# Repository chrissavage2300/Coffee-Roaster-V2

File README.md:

# Coffee-Roaster-V2
My Second DIY coffee roaster

Parts not listed on BOM:

Intake fan: BL4447-04W-B49

https://www.aliexpress.us/item/2251800670595894.html?spm=a2g0o.order_list.order_list_main.29.4b841802Pr1vyz&gatewayAdapt=glo2usa

Exhaust fan: 4090D 12V

https://www.aliexpress.us/item/3256805403626998.html?spm=a2g0o.order_list.order_list_main.195.4b841802Pr1vyz&gatewayAdapt=glo2usa

SSR: GSR1-1-25DA

https://www.aliexpress.us/item/3256802111187964.html?spm=a2g0o.order_list.order_list_main.60.4b841802Pr1vyz&gatewayAdapt=glo2usa

Gears for drum: 1M40T-Bore 6 mm

https://www.aliexpress.us/item/2255800052157775.html?spm=a2g0o.order_list.order_list_main.88.4b841802Pr1vyz&gatewayAdapt=glo2usa

Drum Motor: 12V Single Motor, 66RPM

https://www.aliexpress.us/item/3256805242242724.html?spm=a2g0o.order_list.order_list_main.205.4b841802Pr1vyz&gatewayAdapt=glo2usa

K type thermocouples:

https://finglai.aliexpress.com/store/1100819105?spm=a2g0o.order_list.order_list_main.187.4b841802Pr1vyz

Knobs:

https://www.aliexpress.us/item/3256807011356288.html?spm=a2g0o.order_list.order_list_main.69.4b841802Pr1vyz&gatewayAdapt=glo2usa

LCD

https://www.aliexpress.us/item/2251832723901253.html?spm=a2g0o.order_list.order_list_main.249.4b841802Pr1vyz&gatewayAdapt=glo2usa

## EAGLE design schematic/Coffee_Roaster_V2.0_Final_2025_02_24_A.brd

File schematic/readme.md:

I used Eagle PCB. I will convert further versions to KiCad

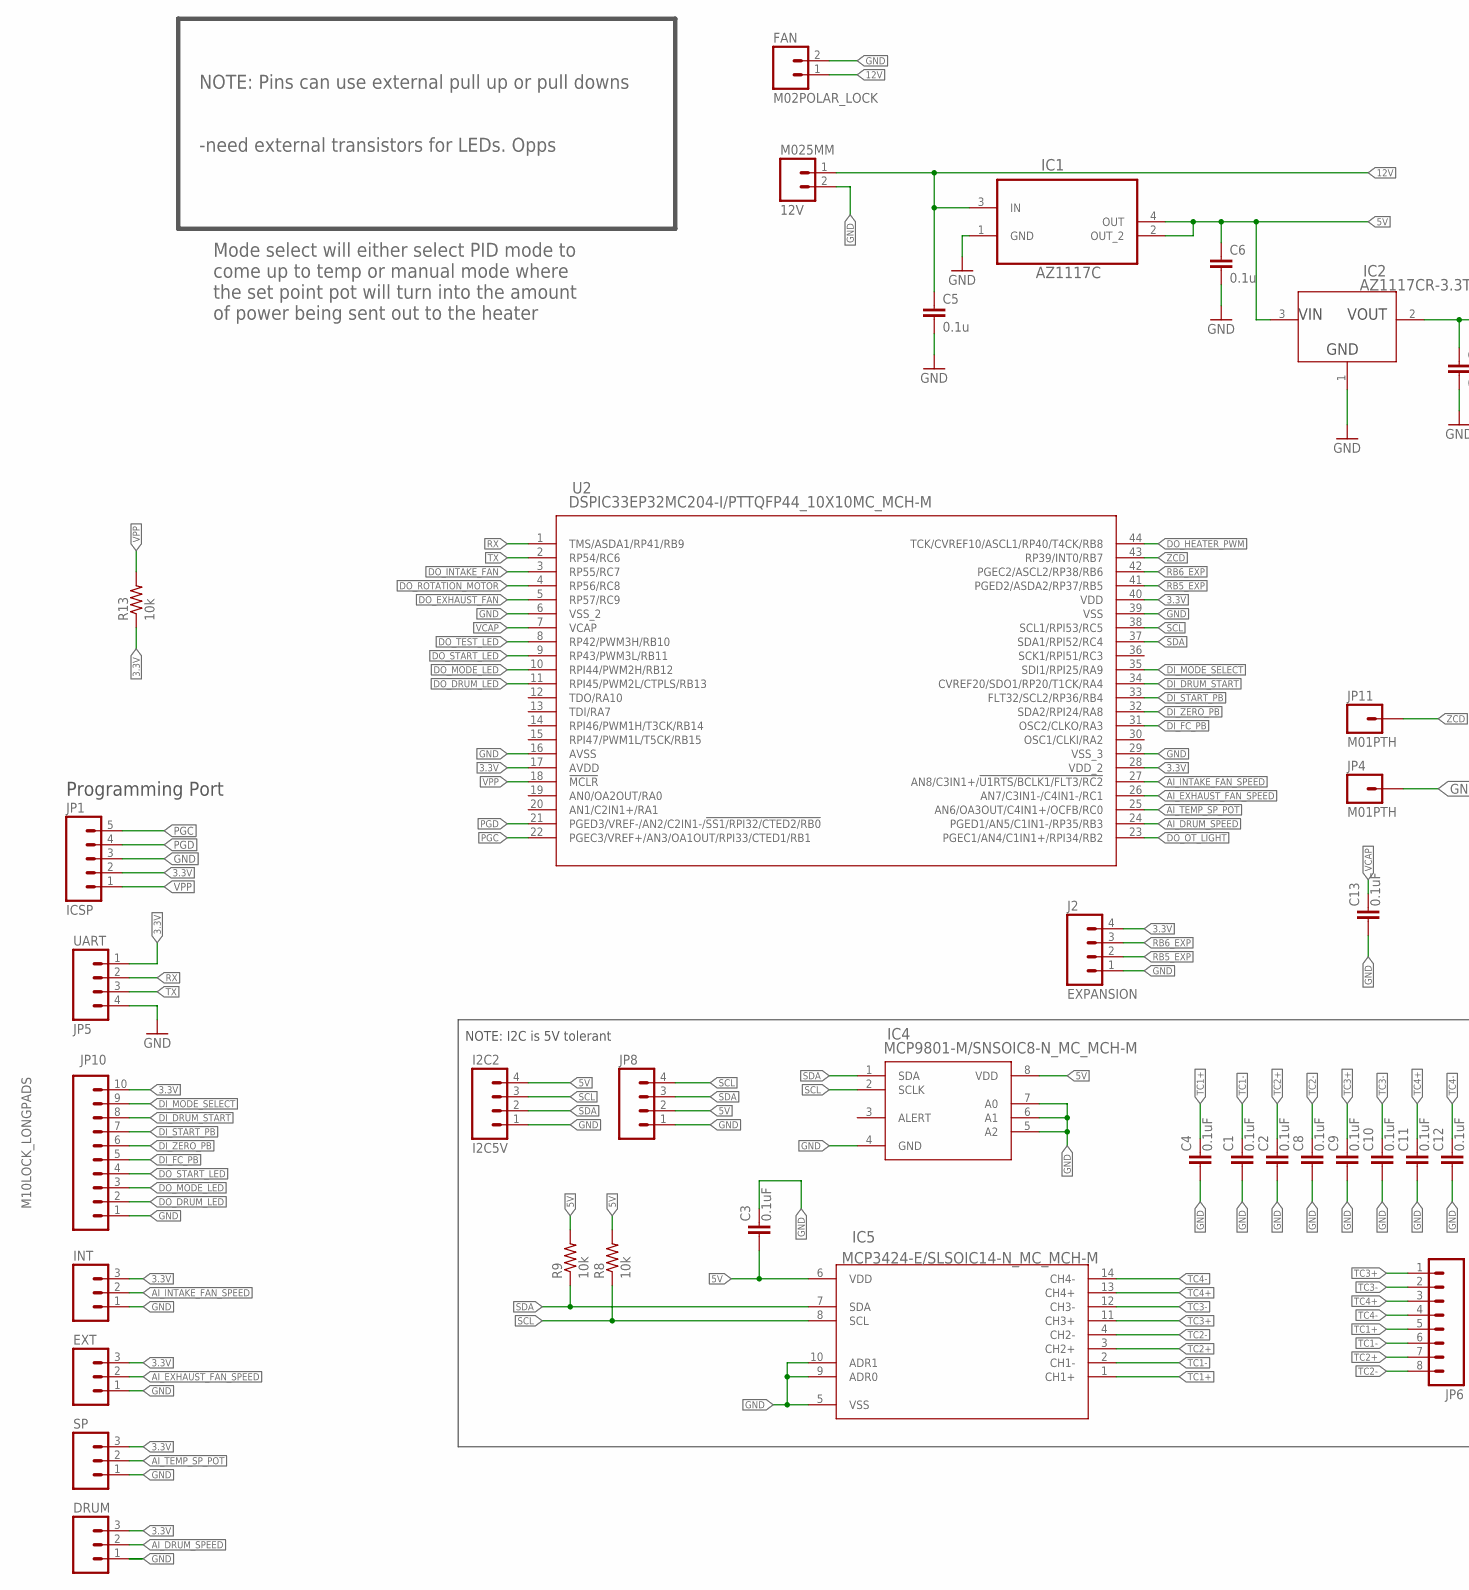
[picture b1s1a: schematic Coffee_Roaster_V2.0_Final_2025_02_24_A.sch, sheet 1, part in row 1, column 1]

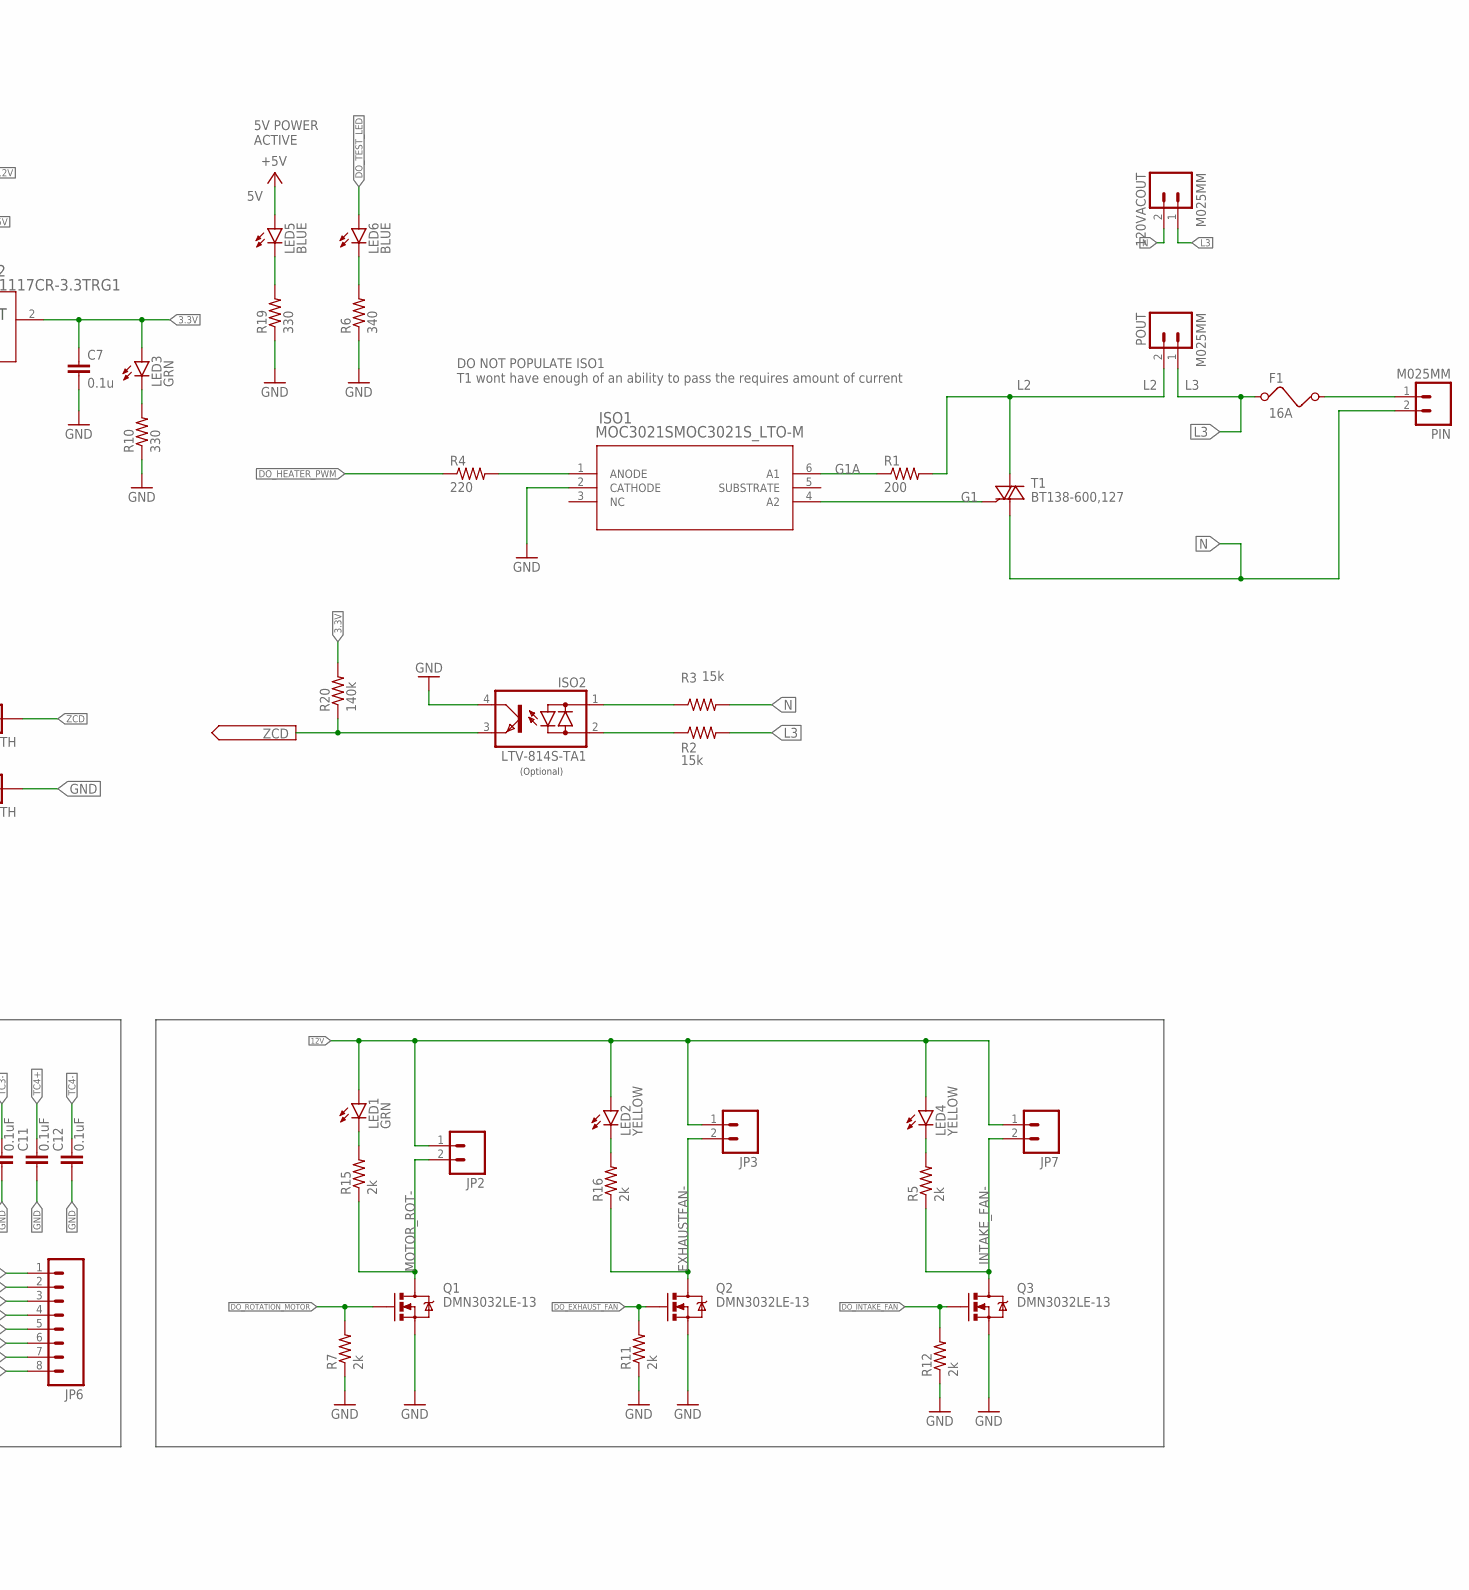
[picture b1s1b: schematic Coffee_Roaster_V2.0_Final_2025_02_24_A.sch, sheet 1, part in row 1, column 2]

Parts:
12V, 120VACOUT: M025MM; SCREWTERMINAL-5MM-2
C1, C2, C3, C4, C8, C9, C10, C11, C12, C13: 0.1uF; 0805
C5, C6, C7: 0.1u; 1206
DRUM: M03POLAR_LOCK; MOLEX-1X3_LOCK
EXT: M03POLAR_LOCK; MOLEX-1X3_LOCK
F1: 16A; FUSE
FAN: M02POLAR_LOCK; MOLEX-1X2_LOCK
I2C2: I2C5V; 1X04-1.5MM_JST
IC1: AZ1117C; SOT230P700X180-4N
IC2: AZ1117CR-3.3TRG1; SOT89_AZ1117_DIO
IC4: MCP9801-M/SNSOIC8-N_MC_MCH-M; SOIC8-N_MC_MCH-M
IC5: MCP3424-E/SLSOIC14-N_MC_MCH-M; SOIC14-N_MC_MCH-M
INT: M03POLAR_LOCK; MOLEX-1X3_LOCK
ISO1: MOC3021SMOC3021S_LTO-M; MOC3021S_LTO-M
ISO2: LTV-814S-TA1; DIL4-SMD
J2: EXPANSION; 1X04-1.5MM_JST
JP1: ICSP; 1X05
JP2, JP3, JP7: M02POLAR_LOCK; MOLEX-1X2_LOCK
JP4, JP11: M01PTH; 1X01
JP5: UART; 1X04_LOCK
JP6: M083.5MM-8; SCREWTERMINAL-3.5MM-8
JP8: M04LOCK_LONGPADS; 1X04_LOCK_LONGPADS
JP10: M10LOCK_LONGPADS; 1X10_LOCK_LONGPADS
LED1, LED3: GRN; LED-1206
LED2, LED4: YELLOW; LED-1206
LED5, LED6: BLUE; LED-1206
PIN: M025MM; SCREWTERMINAL-5MM-2
POUT: M025MM; SCREWTERMINAL-5MM-2
Q1, Q2, Q3: DMN3032LE-13; SOT223
R1: 200; R2512
R2, R3: 15k; R2512
R4: 220; 1206
R5, R7, R11, R12, R15, R16: 2k; 1206
R6: 340; 1206
R8, R9, R13: 10k; M0805
R10, R19: 330; 1206
R20: 140k; 1206
SP: M03POLAR_LOCK; MOLEX-1X3_LOCK
T1: BT138-600,127; TO220BV
U2: DSPIC33EP32MC204-I/PTTQFP44_10X10MC_MCH-M; TQFP44_10X10MC_MCH-M

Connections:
3.3V: C7.1, DRUM.3, EXT.3, IC2.2 (OUTPUT), INT.3, J2.4, JP1.2, JP5.1, JP10.10, LED3.A, R13.1, R20.2, SP.3, U2.17 (AVDD), U2.28 (VDD_2), U2.40 (VDD)
5V: C3.1, C6.1, I2C2.4, IC1.2 (OUT_2), IC1.4 (OUT), IC2.3 (INPUT), IC4.8 (VDD), IC5.6 (VDD), JP8.2, LED5.A, R8.2, R9.2
12V: 12V.1, C5.1, FAN.1, IC1.3 (IN), JP2.1, JP3.1, JP7.1, LED1.A, LED2.A, LED4.A
AI_DRUM_SPEED: DRUM.2, U2.24 (PGED1/AN5/C1IN1-/RP35/RB3)
AI_EXHAUST_FAN_SPEED: EXT.2, U2.26 (AN7/C3IN1-/C4IN1-/RC1)
AI_INTAKE_FAN_SPEED: INT.2, U2.27 (AN8/C3IN1+/!U1RTS/BCLK1/FLT3/RC2)
AI_TEMP_SP_POT: SP.2, U2.25 (AN6/OA3OUT/C4IN1+/OCFB/RC0)
DI_DRUM_START: JP10.8, U2.34 (CVREF20/SDO1/RP20/T1CK/RA4)
DI_FC_PB: JP10.5, U2.31 (OSC2/CLKO/RA3)
DI_MODE_SELECT: JP10.9, U2.35 (SDI1/RPI25/RA9)
DI_START_PB: JP10.7, U2.33 (FLT32/SCL2/RP36/RB4)
DI_ZERO_PB: JP10.6, U2.32 (SDA2/RPI24/RA8)
DO_DRUM_LED: JP10.2, U2.11 (RPI45/PWM2L/CTPLS/RB13)
DO_EXHAUST_FAN: Q2.1 (G), R11.2, U2.5 (RP57/RC9)
DO_HEATER_PWM: R4.1, U2.44 (TCK/CVREF10/ASCL1/RP40/T4CK/RB8)
DO_INTAKE_FAN: Q3.1 (G), R12.2, U2.3 (RP55/RC7)
DO_MODE_LED: JP10.3, U2.10 (RPI44/PWM2H/RB12)
DO_OT_LIGHT: U2.23 (PGEC1/AN4/C1IN1+/RPI34/RB2)
DO_ROTATION_MOTOR: Q1.1 (G), R7.2, U2.4 (RP56/RC8)
DO_START_LED: JP10.4, U2.9 (RP43/PWM3L/RB11)
DO_TEST_LED: LED6.A, U2.8 (RP42/PWM3H/RB10)
EXHAUSTFAN-: JP3.2, Q2.2 (D), Q2.4 (D), R16.1
G1: ISO1.4 (A2), T1.G
G1A: ISO1.6 (A1), R1.1
GND: 12V.2, C1.1, C2.1, C3.2, C4.1, C5.2, C6.2, C7.2, C8.1, C9.1, C10.1, C11.1, C12.1, C13.1, DRUM.1, EXT.1, FAN.2, I2C2.1, IC1.1 (GND), IC2.1 (ADJ/GND), IC4.4 (GND), IC4.5 (A2), IC4.6 (A1), IC4.7 (A0), IC5.5 (VSS), IC5.9 (ADR0), IC5.10 (ADR1), INT.1, ISO1.2 (CATHODE), ISO2.4 (C), J2.1, JP1.3, JP4.1, JP5.4, JP8.1, JP10.1, Q1.3 (S), Q2.3 (S), Q3.3 (S), R6.1, R7.1, R10.1, R11.1, R12.1, R19.1, SP.1, U2.6 (VSS_2), U2.16 (AVSS), U2.29 (VSS_3), U2.39 (VSS)
INTAKE_FAN-: JP7.2, Q3.2 (D), Q3.4 (D), R5.1
L1: F1.2, PIN.1
L2: POUT.2, R1.2, T1.T2 (A2)
L3: 120VACOUT.1, F1.1, POUT.1, R2.2
MOTOR_ROT-: JP2.2, Q1.2 (D), Q1.4 (D), R15.1
N: 120VACOUT.2, PIN.2, R3.2, T1.T1 (A1)
unnamed: ISO1.1 (ANODE), R4.2
unnamed: LED3.C, R10.2
unnamed: LED1.C, R15.2
unnamed: LED2.C, R16.2
unnamed: ISO2.1 (AC1), R3.1
unnamed: ISO2.2 (AC2), R2.1
unnamed: LED4.C, R5.2
unnamed: LED6.C, R6.2
unnamed: LED5.C, R19.2
PGC: JP1.5, U2.22 (PGEC3/VREF+/AN3/OA1OUT/RPI33/CTED1/RB1)
PGD: JP1.4, U2.21 (PGED3/VREF-/AN2/C2IN1-/!SS1/RPI32/CTED2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)
RB5_EXP: J2.2, U2.41 (PGED2/ASDA2/RP37/RB5)
RB6_EXP: J2.3, U2.42 (PGEC2/ASCL2/RP38/RB6)
RX: JP5.2, U2.1 (TMS/ASDA1/RP41/RB9)
SCL: I2C2.3, IC4.2 (SCLK), IC5.8 (SCL), JP8.4, R8.1, U2.38 (SCL1/RPI53/RC5)
SDA: I2C2.2, IC4.1 (SDA), IC5.7 (SDA), JP8.3, R9.1, U2.37 (SDA1/RPI52/RC4)
TC1+: C4.2, IC5.1 (CH1+), JP6.5
TC1-: C1.2, IC5.2 (CH1-), JP6.6
TC2+: C2.2, IC5.3 (CH2+), JP6.7
TC2-: C8.2, IC5.4 (CH2-), JP6.8
TC3+: C9.2, IC5.11 (CH3+), JP6.1
TC3-: C10.2, IC5.12 (CH3-), JP6.2
TC4+: C11.2, IC5.13 (CH4+), JP6.3
TC4-: C12.2, IC5.14 (CH4-), JP6.4
TX: JP5.3, U2.2 (RP54/RC6)
VCAP: C13.2, U2.7 (VCAP)
VPP: JP1.1, R13.2, U2.18 (!MCLR)
ZCD: ISO2.3 (E), JP11.1, R20.1, U2.43 (RP39/INT0/RB7)

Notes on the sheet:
Programming Port
5V POWER ACTIVE
(Optional)
NOTE: Pins can use external pull up or pull downs -need external transistors for LEDs. Opps
NOTE: I2C is 5V tolerant
Mode select will either select PID mode to come up to temp or manual mode where the set point pot will turn into the amount of power being sent out to the heater
DO NOT POPULATE ISO1 T1 wont have enough of an ability to pass the requires amount of current

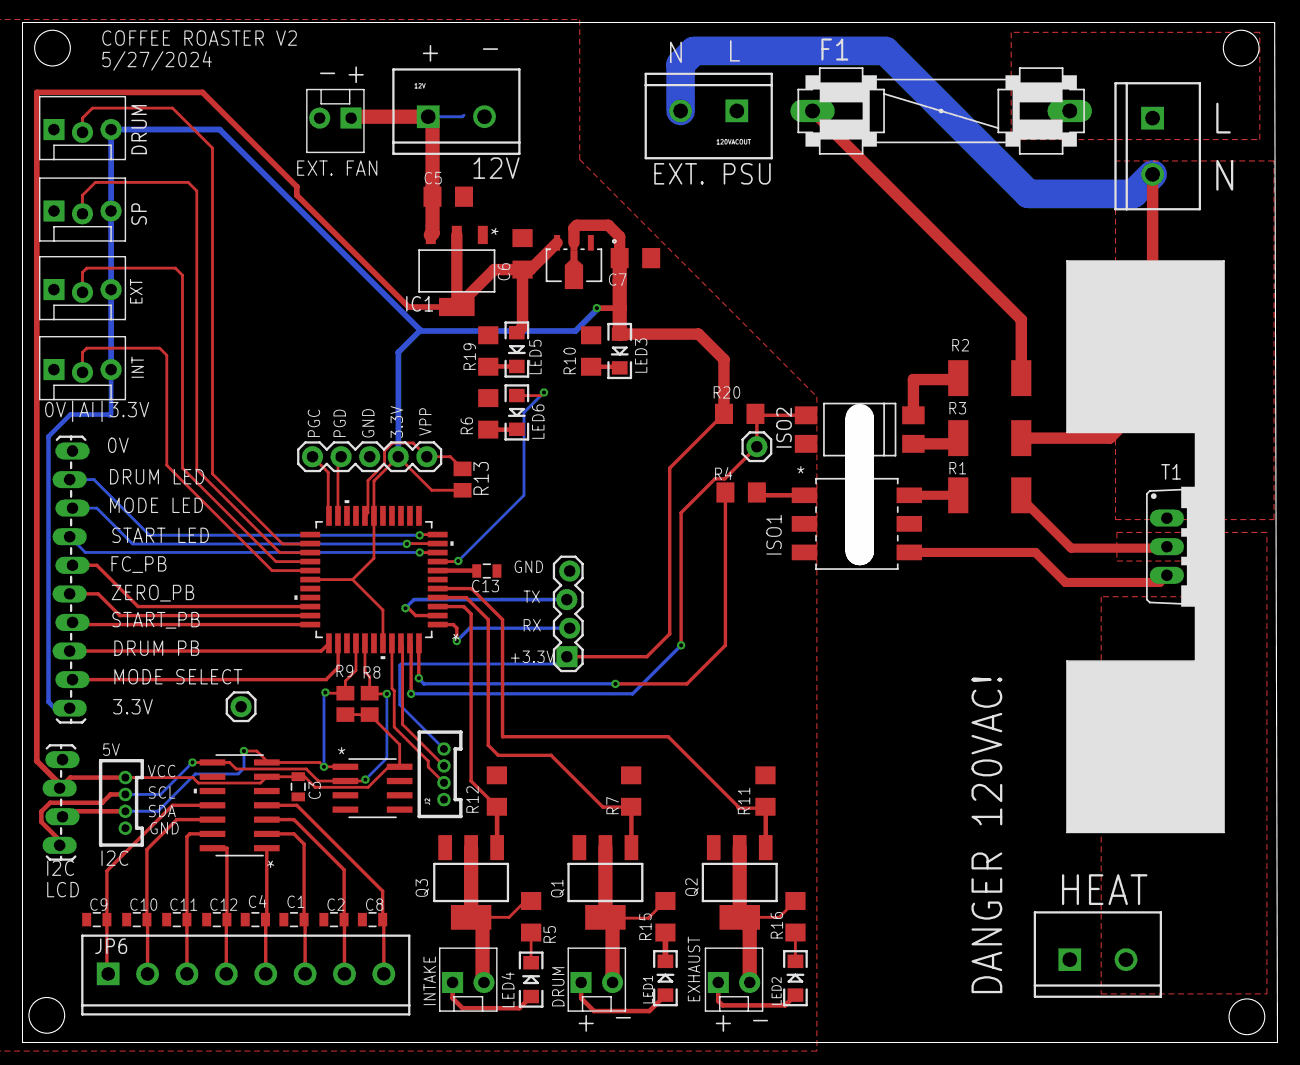
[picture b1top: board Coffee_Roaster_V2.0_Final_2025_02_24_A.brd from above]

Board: 2 copper layers, 109.0 x 88.1 mm, 70 parts (0 on the bottom side), 58 nets.

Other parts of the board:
HEATSINK: 7-345-2PP-BA

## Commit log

2026-02-20 Add files via upload
    code added

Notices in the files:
parts and their libraries:
SparkFun-Capacitors: Licensing: Creative Commons ShareAlike 4.0 International - https://creativecommons.org/licenses/by-sa/4.0
SparkFun: Licensing: CC v3.0 Share-Alike You are welcome to use this library for commercial purposes.
COPYRIGHT: Copyright (C) 2018 Accelerated Designs. All rights reserved
